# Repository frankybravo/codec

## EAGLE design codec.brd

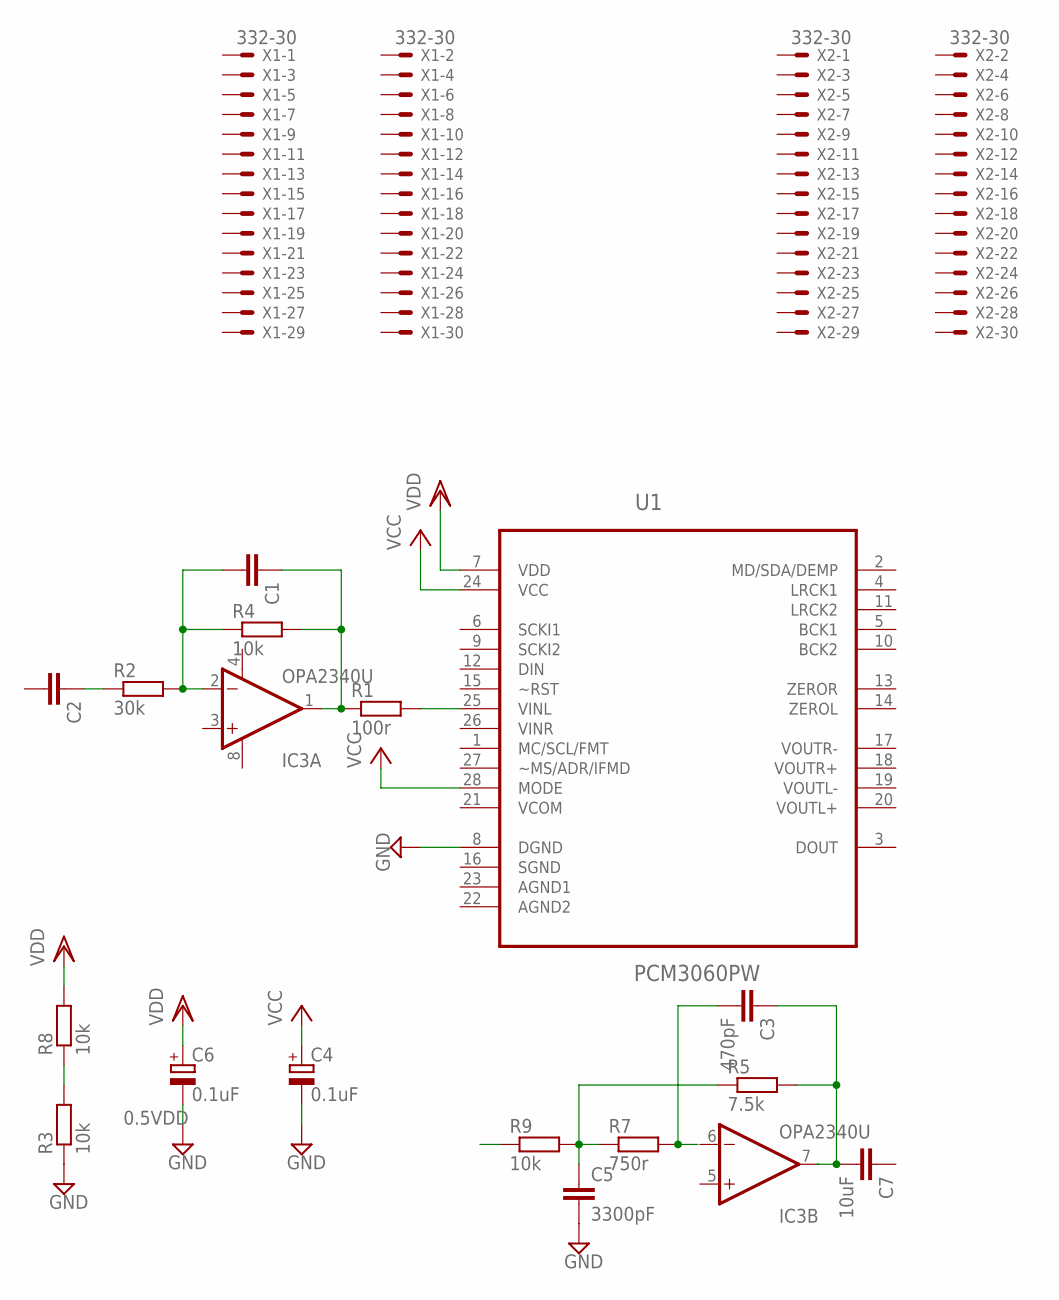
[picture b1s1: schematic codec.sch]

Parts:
C1, C2: C-EUC1608; C1608
C3: 470pF; C1608
C4, C6: 0.1uF; 150CLZ-1010
C5: 3300pF; C1608
C7: 10uF; C1608
IC3: OPA2340U; SO08
R1: 100r; R1206
R2: 30k; R1206
R3, R4, R8, R9: 10k; R1206
R5: 7.5k; R1206
R7: 750r; R1206
U1: PCM3060PW; SOP65P640X120-28N
X1, X2: 332-30

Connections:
0.5VDD: R3.2, R8.1
GND: C4.-, C5.2, C6.-, R3.1, U1.8 (DGND)
unnamed: C1.1, IC3.1 (OUT), R1.1, R4.2
unnamed: C2.1, R2.1
unnamed: C1.2, IC3.2 (-IN), R2.2, R4.1
unnamed: C3.1, C7.2, IC3.7 (OUT), R5.2
unnamed: C3.2, R7.2
unnamed: C5.1, R5.1, R7.1, R9.2
unnamed: R1.2, U1.25 (VINL)
V+: IC3.8 (V+)
V-: IC3.4 (V-)
VCC: C4.+, U1.24 (VCC), U1.28 (MODE)
VDD: C6.+, R8.2, U1.7 (VDD)

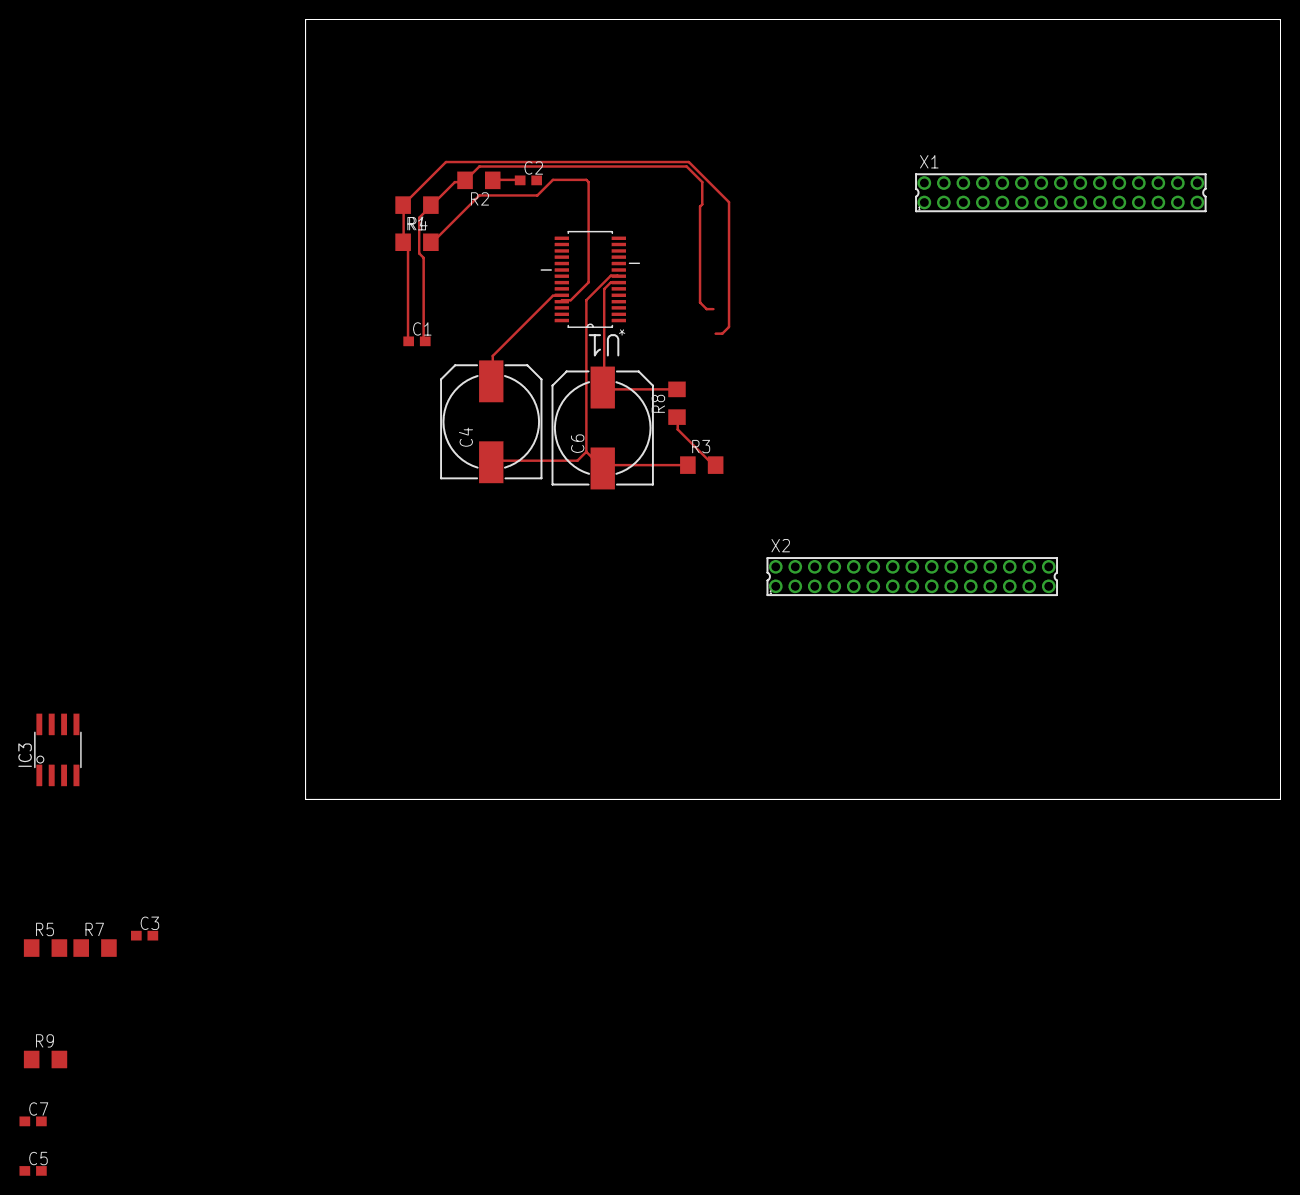
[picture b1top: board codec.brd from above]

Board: 2 copper layers, 100.0 x 80.0 mm, 19 parts (0 on the bottom side), 11 nets.

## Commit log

2016-01-02 first cut
